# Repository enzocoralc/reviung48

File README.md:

# reviung48
 Based on the [reviung41](https://github.com/gtips/reviung "Reviung41") with a split spacebar and left num row.
For the assembly guide, follow [reviung41 guide](https://reviung.com/build-guide/391/ "guide").

### main pcb

### plate pcb

### backplate pcb

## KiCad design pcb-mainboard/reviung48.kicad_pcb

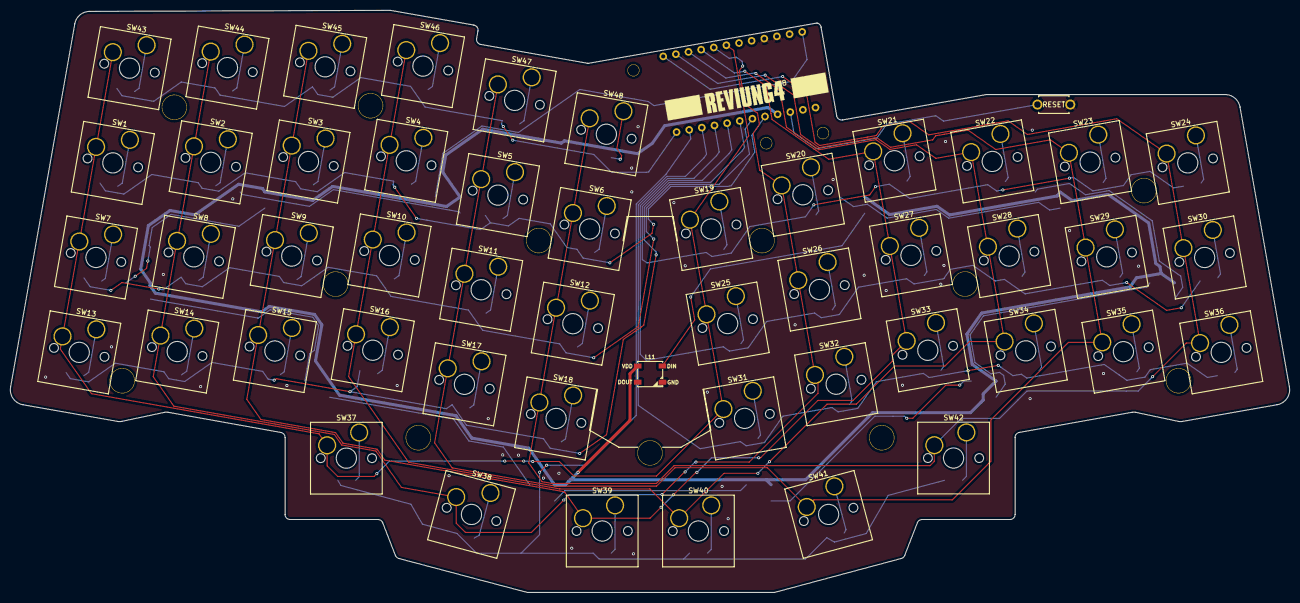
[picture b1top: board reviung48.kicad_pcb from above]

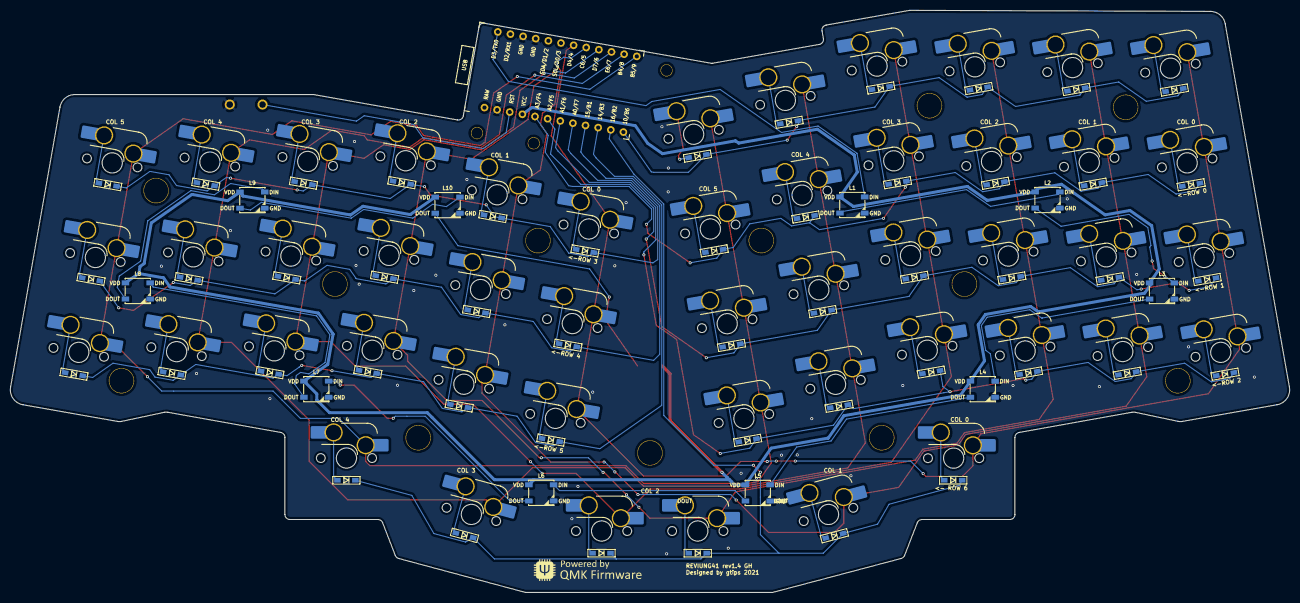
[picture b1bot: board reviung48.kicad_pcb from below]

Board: 2 copper layers, 253.3 x 115.3 mm, 123 parts (62 on the bottom side), 76 nets.

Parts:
D1, D1#2, D2, D2#2, D3, D3#2, D4, D4#2, D5, D5#2, D6, D6#2, D7, D8, D9, D10, D11, D12, D13, D14, D15, D16, D17, D18, D19, D20, D21, D22, D23, D24, D25, D26, D27, D28, D29, D30, D31, D32, D33, D34, D35, D36, D37, D38, D39, D39#2, D40, D41: 1N4148W; D3_SMD_1side
H1: H1; HOLE
H2: H2; HOLE
H3: H3; HOLE
H4: H4; HOLE
H5: H5; HOLE
H6: H6; HOLE
H7: H7; HOLE
H8: H8; HOLE
H9: H9; HOLE
H10: H10; HOLE
H11: H11; HOLE
H12: H12; HOLE_2.2mm
H13: H13; HOLE_2.2mm
H14: H14; HOLE_2.2mm
L1, L2, L3, L4, L5, L6, L7, L8, L9, L10, L11: WS2812B; LED_WS2812B_PLCC4_5.0x5.0mm_P3.2mm
RESET1: SW_PUSH; ResetSW_1side
SW1, SW2, SW3, SW4, SW5, SW6, SW7, SW8, SW9, SW10, SW11, SW12, SW13, SW14, SW15, SW16, SW17, SW18, SW19, SW20, SW21, SW22, SW23, SW24, SW25, SW26, SW27, SW28, SW29, SW30, SW31, SW32, SW33, SW34, SW35, SW36, SW37, SW38, SW41, SW42, SW43, SW44, SW45, SW46, SW47, SW48: SW_PUSH; SW_Hotswap_Kailh_MX_plated
SW39, SW40: SW_2U_PUSH; SW_Hotswap_Kailh_MX_plated
U1: ProMicro

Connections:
GND: L1.3, L2.3, L3.3, L4.3, L5.3, L6.3, L7.3, L8.3, L9.3, L10.3, L11.3, RESET1.2, U1.3, U1.4, U1.23
LED: L1.4, U1.1
Ned-(D44-Pad2): D2#2.2, SW44.2
unnamed: D1.2, SW1.2
unnamed: D2.2, SW2.2
unnamed: D3.2, SW3.2
unnamed: D4.2, SW4.2
unnamed: D5.2, SW5.2
unnamed: D6.2, SW6.2
unnamed: D7.2, SW7.2
unnamed: D8.2, SW8.2
unnamed: D9.2, SW9.2
unnamed: D10.2, SW10.2
unnamed: D11.2, SW11.2
unnamed: D12.2, SW12.2
unnamed: D13.2, SW13.2
unnamed: D14.2, SW14.2
unnamed: D15.2, SW15.2
unnamed: D16.2, SW16.2
unnamed: D17.2, SW17.2
unnamed: D18.2, SW18.2
unnamed: D19.2, SW19.2
unnamed: D20.2, SW20.2
unnamed: D21.2, SW21.2
unnamed: D22.2, SW22.2
unnamed: D23.2, SW23.2
unnamed: D24.2, SW24.2
unnamed: D25.2, SW25.2
unnamed: D26.2, SW26.2
unnamed: D27.2, SW27.2
unnamed: D28.2, SW28.2
unnamed: D29.2, SW29.2
unnamed: D30.2, SW30.2
unnamed: D31.2, SW31.2
unnamed: D32.2, SW32.2
unnamed: D33.2, SW33.2
unnamed: D34.2, SW34.2
unnamed: D35.2, SW35.2
unnamed: D36.2, SW36.2
unnamed: D37.2, SW37.2
unnamed: D38.2, SW38.2
unnamed: D39.2, SW39.2
unnamed: D39#2.2, SW40.2
unnamed: D40.2, SW41.2
unnamed: D41.2, SW42.2
unnamed: D1#2.2, SW43.2
unnamed: D3#2.2, SW45.2
unnamed: D4#2.2, SW46.2
unnamed: D5#2.2, SW47.2
unnamed: D6#2.2, SW48.2
unnamed: L1.2, L2.4
unnamed: L2.2, L3.4
unnamed: L3.2, L4.4
unnamed: L4.2, L5.4
unnamed: L5.2, L6.4
unnamed: L6.2, L7.4
unnamed: L7.2, L8.4
unnamed: L8.2, L9.4
unnamed: L10.2, L11.4
unnamed: L9.2, L10.4
VCC: L1.1, L2.1, L3.1, L4.1, L5.1, L6.1, L7.1, L8.1, L9.1, L10.1, L11.1, U1.21
col0: SW1.1, SW7.1, SW13.1, SW19.1, SW25.1, SW31.1, SW37.1, SW43.1, U1.7
col1: SW2.1, SW8.1, SW14.1, SW20.1, SW26.1, SW32.1, SW38.1, SW44.1, U1.8
col2: SW3.1, SW9.1, SW15.1, SW21.1, SW27.1, SW33.1, SW39.1, SW45.1, U1.9
col3: SW4.1, SW10.1, SW16.1, SW22.1, SW28.1, SW34.1, SW40.1, SW46.1, U1.10
col4: SW5.1, SW11.1, SW17.1, SW23.1, SW29.1, SW35.1, SW41.1, SW47.1, U1.11
col5: SW6.1, SW12.1, SW18.1, SW24.1, SW30.1, SW36.1, SW42.1, SW48.1, U1.12
reset: RESET1.1, U1.22
row0: D1.1, D2.1, D3.1, D4.1, D5.1, D6.1, U1.20
row1: D7.1, D8.1, D9.1, D10.1, D11.1, D12.1, U1.19
row2: D13.1, D14.1, D15.1, D16.1, D17.1, D18.1, U1.18
row3: D19.1, D20.1, D21.1, D22.1, D23.1, D24.1, U1.17
row4: D25.1, D26.1, D27.1, D28.1, D29.1, D30.1, U1.16
row5: D31.1, D32.1, D33.1, D34.1, D35.1, D36.1, U1.15
row6: D37.1, D38.1, D39.1, D39#2.1, D40.1, D41.1, U1.14
row7: D1#2.1, D2#2.1, D3#2.1, D4#2.1, D5#2.1, D6#2.1, U1.13

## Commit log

2022-11-19 added the files
2022-11-19 finished pcb
    v2 is slightly better edgecut than v1
2022-11-19 fixed screw hole position
2022-11-19 fixed pcb folder names
2022-11-21 finished pcb and plate
    fixed edgecuts, promicro position, promicro cover and some wiring
2022-11-22 cleaned the repo and the readme
2022-11-22 fixed the pcbs
2022-11-22 added pictures to the readme
2022-11-22 fixed pcb-plate and pic
2022-11-22 updated the readme
2022-11-22 fixed all the readme
